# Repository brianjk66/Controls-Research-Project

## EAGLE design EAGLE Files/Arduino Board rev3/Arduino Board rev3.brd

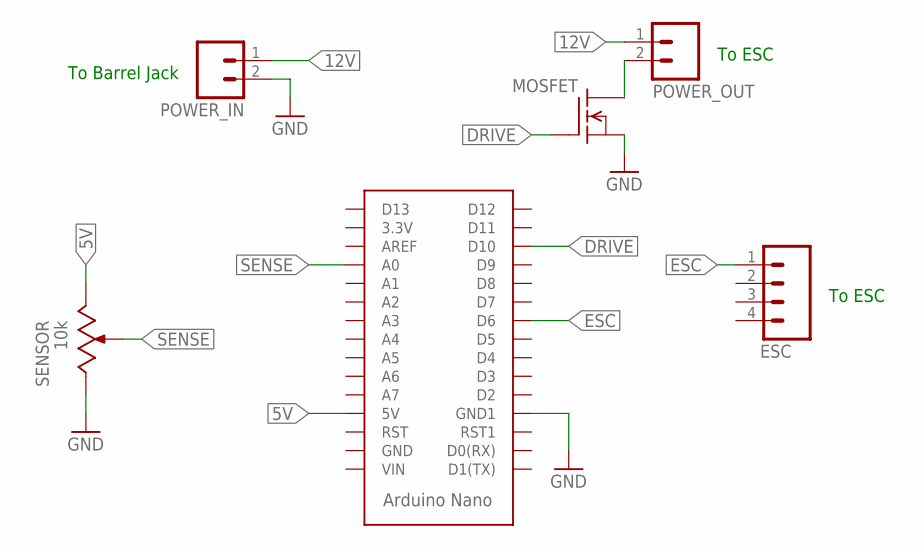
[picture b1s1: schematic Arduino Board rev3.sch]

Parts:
ARDUINO_NANO: ARDUINO_NANO
ESC: M04; 1X04
MOSFET: N-CHANNEL_MOSFETGENERIC; TO-220-SINK
POWER_IN: M02; 1X02
POWER_OUT: M02; 1X02
SENSOR: 10k; SV03A

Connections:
5V: ARDUINO_NANO.5V, SENSOR.3 (A)
12V: POWER_IN.1, POWER_OUT.1
DRIVE: ARDUINO_NANO.D10, MOSFET.1 (G)
ESC: ARDUINO_NANO.D6, ESC.1
GND: ARDUINO_NANO.GND1, MOSFET.3 (S), POWER_IN.2, SENSOR.1 (E)
unnamed: MOSFET.2 (D), POWER_OUT.2
SENSE: ARDUINO_NANO.A0, SENSOR.2 (S), SENSOR.2.1 (S)

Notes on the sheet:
To Barrel Jack
To ESC

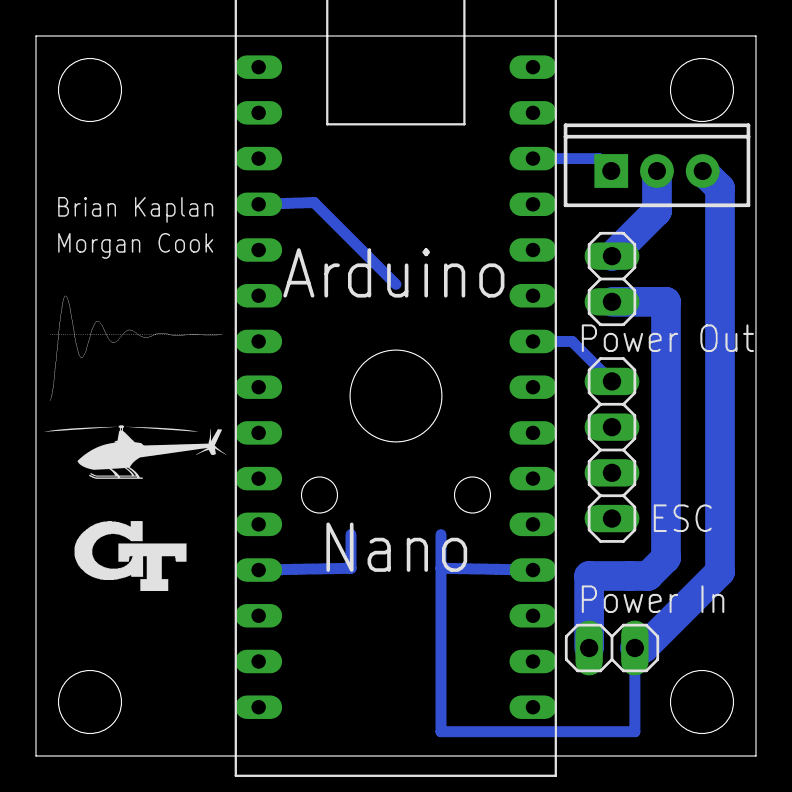
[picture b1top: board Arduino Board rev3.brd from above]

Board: 2 copper layers, 40.0 x 40.0 mm, 6 parts (1 on the bottom side), 7 nets.

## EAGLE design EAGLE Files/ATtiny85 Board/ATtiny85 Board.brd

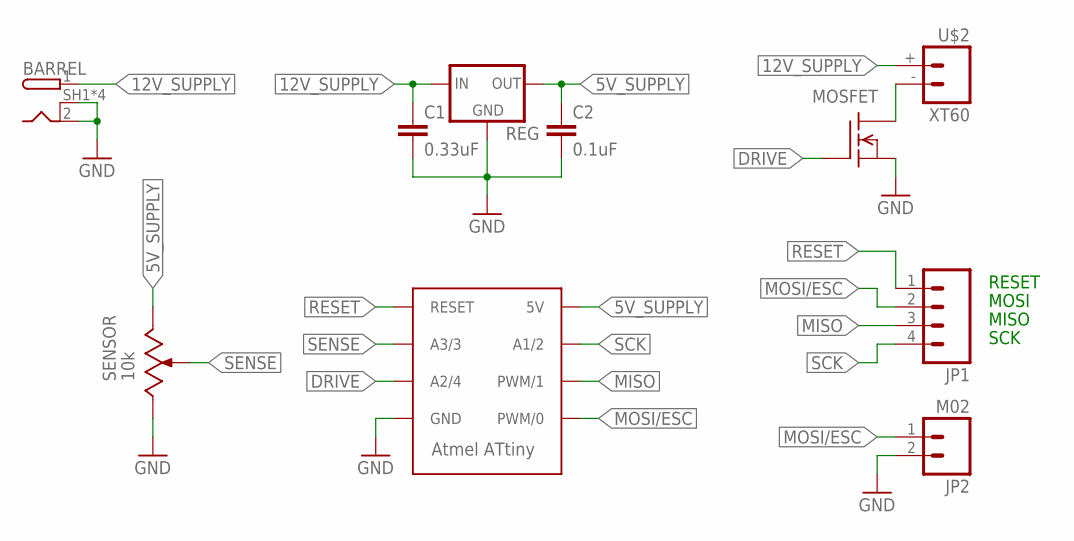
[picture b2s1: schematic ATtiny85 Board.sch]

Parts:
BARREL: PJ-082BH
C1: 0.33uF; 0805
C2: 0.1uF; 0805
JP1: M04; 1X04
JP2: M02; 1X02
MOSFET: SI2312; SOT-23
REG: L78L; SOT-89
SENSOR: 10k; SV03A
U$1: ATTINY; 8S2
U$2: XT60

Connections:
5V_SUPPLY: C2.1, REG.1 (OUT), SENSOR.1 (E), U$1.8 (5V)
12V_SUPPLY: BARREL.1 (PWR), C1.1, REG.3 (IN), U$2.+ (2)
DRIVE: MOSFET.1 (G), U$1.3 (A2/4)
GND: BARREL.2 (GND), BARREL.SH1 (SHIELD), BARREL.SH2 (SHIELD), BARREL.SH3 (SHIELD), BARREL.SH4 (SHIELD), C1.2, C2.2, JP2.2, MOSFET.2 (S), REG.2 (GND), REG.2.1 (GND), REG.2.2 (GND), SENSOR.3 (A), U$1.4 (GND)
MISO: JP1.3, U$1.6 (PWM/1)
MOSI/ESC: JP1.2, JP2.1, U$1.5 (PWM/0)
unnamed: MOSFET.3 (D), U$2.- (1)
RESET: JP1.1, U$1.1 (RESET)
SCK: JP1.4, U$1.7 (A1/2)
SENSE: SENSOR.2 (S), SENSOR.2.1 (S), U$1.2 (A3/3)

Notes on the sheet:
RESET
MOSI
MISO
SCK

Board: 2 copper layers, 10 parts (0 on the bottom side), 10 nets, no tracks yet.

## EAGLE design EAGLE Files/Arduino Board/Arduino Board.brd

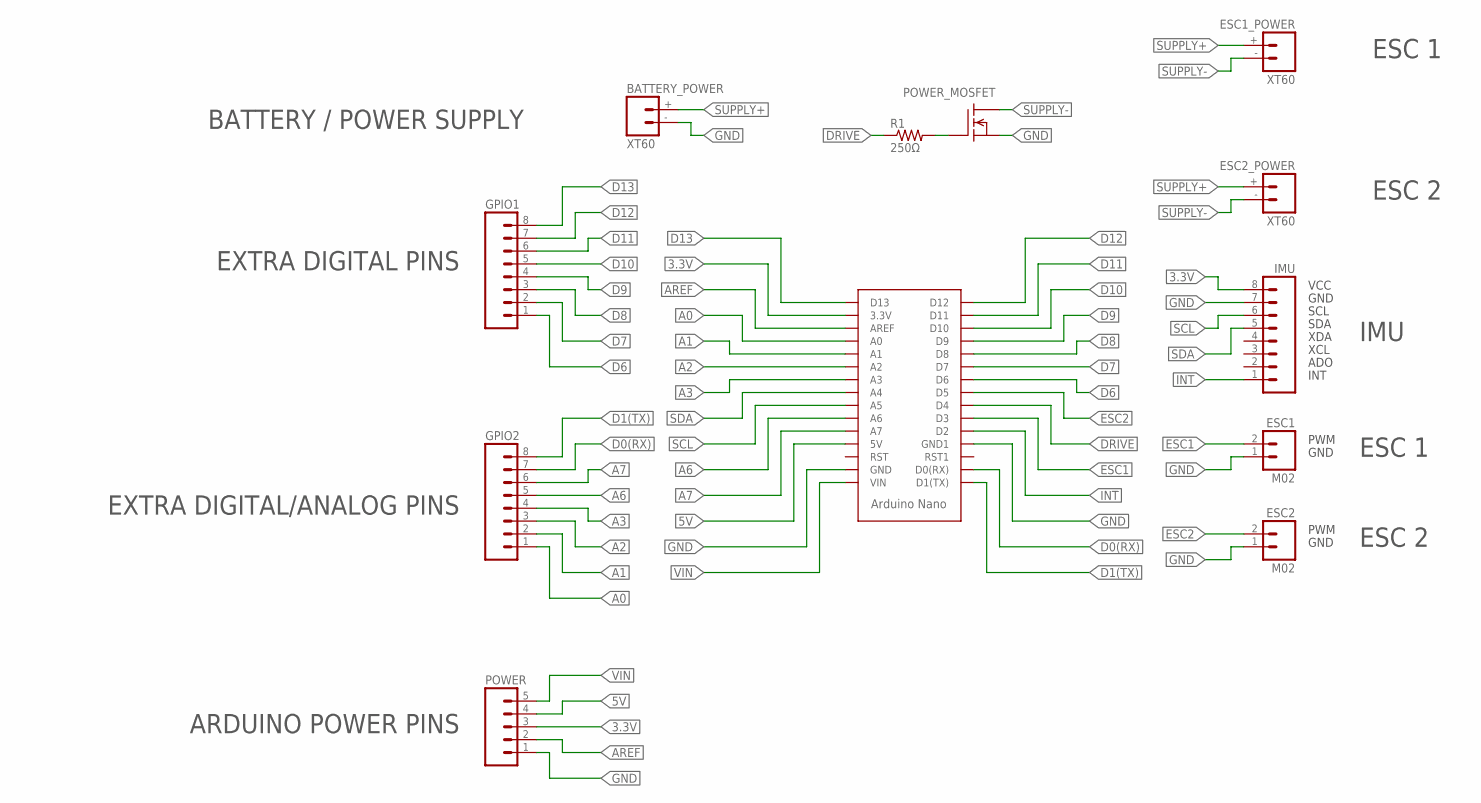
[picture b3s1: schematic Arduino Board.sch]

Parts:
BATTERY_POWER: XT60
ESC1, ESC2: M02; 1X02
ESC1_POWER, ESC2_POWER: XT60
GPIO1, GPIO2: M08; 1X08
IMU: M08; 1X08
POWER: M05; 1X05
POWER_MOSFET: N-CHANNEL_MOSFETGENERIC; TO-220-SINK
R1: 250Ω; AXIAL-0.4
U$1: ARDUINO_NANO

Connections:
3.3V: IMU.8, POWER.3, U$1.3.3V
5V: POWER.4, U$1.5V
A0: GPIO2.1, U$1.A0
A1: GPIO2.2, U$1.A1
A2: GPIO2.3, U$1.A2
A3: GPIO2.4, U$1.A3
A6: GPIO2.5, U$1.A6
A7: GPIO2.6, U$1.A7
AREF: POWER.2, U$1.AREF
D0(RX): GPIO2.7, U$1.D0(RX)
D1(TX): GPIO2.8, U$1.D1(TX)
D6: GPIO1.1, U$1.D6
D7: GPIO1.2, U$1.D7
D8: GPIO1.3, U$1.D8
D9: GPIO1.4, U$1.D9
D10: GPIO1.5, U$1.D10
D11: GPIO1.6, U$1.D11
D12: GPIO1.7, U$1.D12
D13: GPIO1.8, U$1.D13
DRIVE: R1.P$1 (1), U$1.D4
ESC1: ESC1.2, U$1.D3
ESC2: ESC2.2, U$1.D5
GND: BATTERY_POWER.- (1), ESC1.1, ESC2.1, IMU.7, POWER.1, POWER_MOSFET.3 (S), U$1.GND, U$1.GND1
INT: IMU.1, U$1.D2
unnamed: POWER_MOSFET.1 (G), R1.P$2 (2)
SCL: IMU.6, U$1.A5
SDA: IMU.5, U$1.A4
SUPPLY+: BATTERY_POWER.+ (2), ESC1_POWER.+ (2), ESC2_POWER.+ (2)
SUPPLY-: ESC1_POWER.- (1), ESC2_POWER.- (1), POWER_MOSFET.2 (D)
VIN: POWER.5, U$1.VIN

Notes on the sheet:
VCC
GND
SCL
SDA
XDA
XCL
ADO
INT
PWM
ESC 1
ESC 2
IMU
BATTERY / POWER SUPPLY
EXTRA DIGITAL PINS
EXTRA DIGITAL/ANALOG PINS
ARDUINO POWER PINS

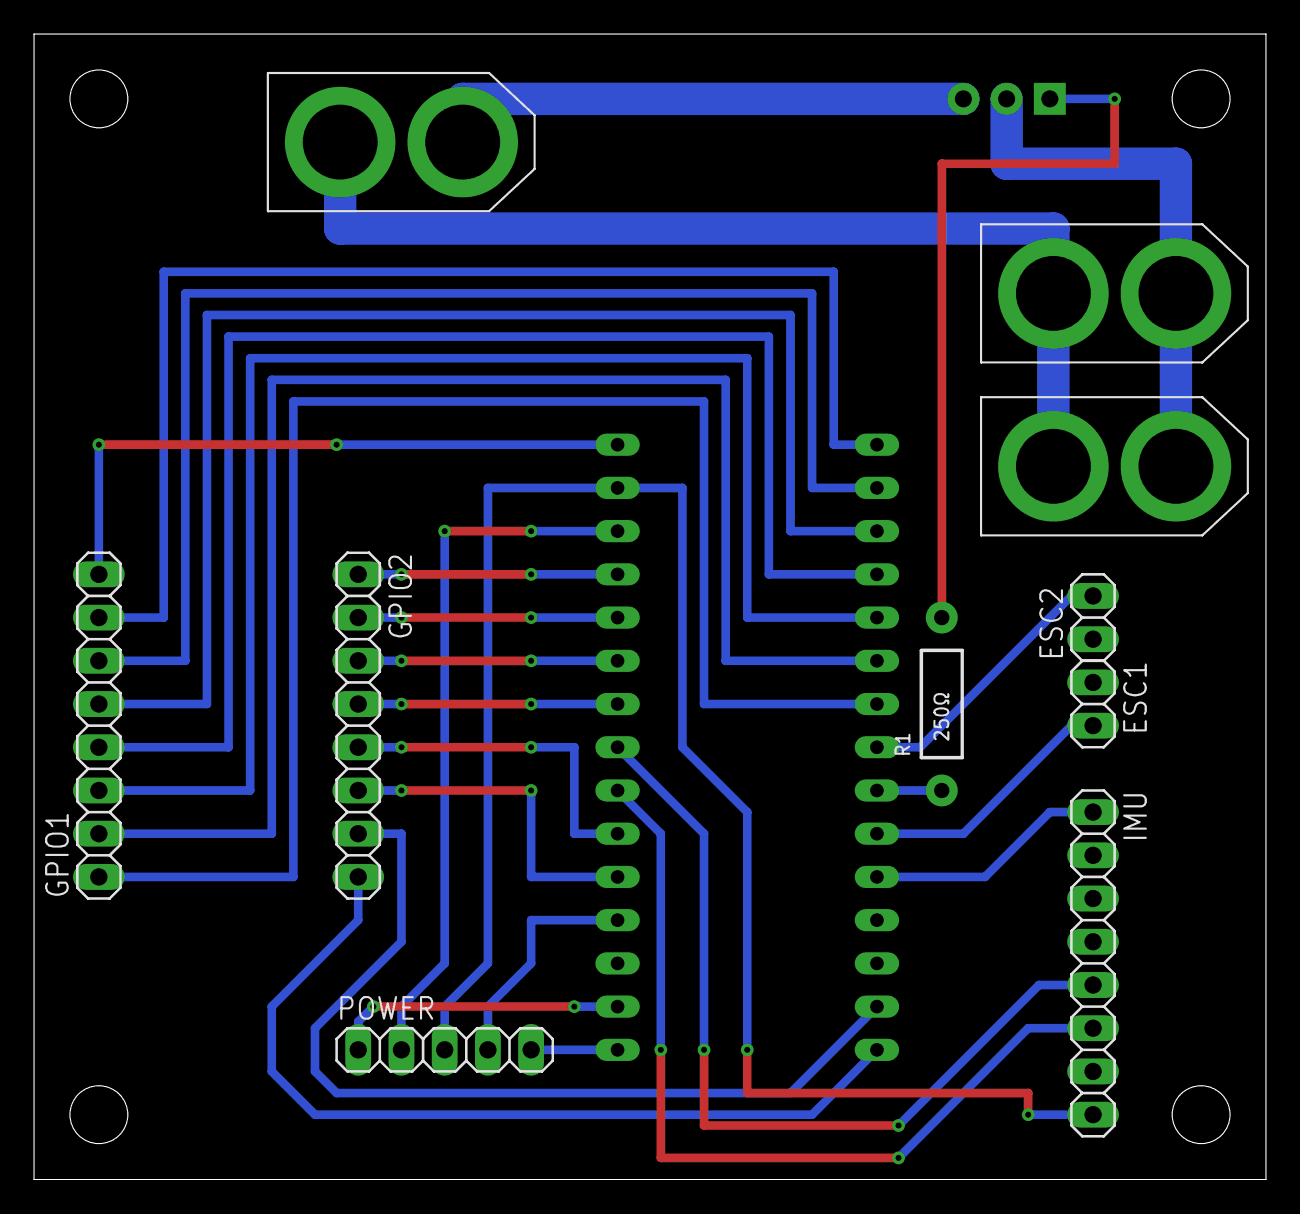
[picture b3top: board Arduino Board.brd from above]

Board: 2 copper layers, 72.4 x 67.3 mm, 12 parts (1 on the bottom side), 30 nets.

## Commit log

2017-11-17 Initial Commit of Current Project
    Arduino files, ordered parts, and other project files
2017-11-17 Test Commit
2017-11-17 CAD files initial upload
2017-11-17 Removed git commit test file
2017-11-17 Renamed CAD files
2017-11-17 Enlarged center hole for both MMs
2017-11-18 Reorganized CAD files
2017-11-18 Added 2MM gcode, .2mm layer thickness
2017-11-18 Fixed mounting hole problem
2017-11-18 Added gcode for DMM
2017-11-19 Added gcodes for 3D printing the arm and roll lock
2017-11-19 Added preliminary code for dual motor configuration
2017-11-19 Added dual motor pitch controller (gains are NOT tuned)
2017-11-21 Added rotating base 3D files
2017-11-21 Ok REALLY adding in the rotating base this time. Sorry.
2017-11-22 Added base to our files
2017-12-01 Created prelimiary PCB design to house project's microcontroller and electrical components
2017-12-01 Small modification to PID function to constrain value of iState more easily
2017-12-10 Added gitignore for EAGLE backup files (.b#2, .s#5, etc.)
2017-12-10 Tweaked gains, added constrain() function to PID integrator, and added cosine to thrust drive signal
2017-12-10 Small typo fix
2017-12-10 Corrected schematic error where MOSFET was wired incorrectly in circuit
2017-12-10 Added Arduino sketch for testing control of power MOSFET
2017-12-10 Fixed untracked files
2017-12-10 Added library file backups to .gitignore
2017-12-11 Updated default PID gains to more stable values
2017-12-11 Added voltage divider for simple battery monitoring
2017-12-16 Updated itemized receipts spreadsheet and added new order invoices
2017-12-18 Updated part orders spreadsheet and invoices
2017-12-29 Added new Hobby King and Banggood Orders to itemized receipts sheet
2018-01-07 Added barrel jack order from Digi-Key to itemized receipts spreadsheet
2018-01-07 Small fix to .gitignore file
2018-01-18 Added new Arrow order to itemized receipts spreadsheet
2018-01-18 Small changes to PCB design files from EAGLE software update
2018-01-18 Added new EAGLE design files for ATtiny85-based PCB
2018-01-18 Added new components to library for ATtiny85 PCB design
2018-01-18 Modified Rotating Base part to have fully parametrized dimensions and features
2018-01-21 Added new Arduino code for testing ESC control with the ATtiny85
2018-01-21 Updated BOM with headers and connectors
2018-01-25 Added several new sketches for testing the ATtiny85 with PWM, Serial, PID control, etc.
2018-01-25 Small fix to a few packages in library
2018-01-25 Enlarged and repositioned vias for easier milling and soldering
2018-01-25 Added standoffs to BOM and quotes from PCB fabrication and assembly plants
2018-01-25 New Base
2018-01-26 Cleaned up repository and modified .gitignore
2018-02-04 Updated .gitignore for Thumb.db Windows file
2018-02-04 Modified base with towers, made base with open slots for towers, made towers.
2018-02-04 Moved the Tower.stl file back to the 3D print files folder from SolidWorks Parts
2018-02-04 Fixed dimensions for printing on base and towers
2018-02-04 Reorganized .stl and .SLDPRT files into old Dual Motor, Misc (single motor included), and Teensy Configuration.
2018-02-04 Added single motor arm without a shaft. Potentially accidentally modified Arm.SLDPRT in Dual Motor and Single Motor Mount.SLDPRT in Misc.
2018-02-05 Actually added shaft.
2018-02-05 Made shaft size bigger, added a configuration for the arm file for 150mm with a centered ESC sheath, created a separate .STL file for it.
2018-02-05 Resized the square on shaft from 5.3mm to 4.9mm.
2018-02-05 Restructured software directory to distinguish between software for different microcontrollers (Arduino, ATtiny, and Teensy)
2018-02-05 Updated library to include the Teensy 3.2
2018-02-05 Created new PCB design for Teensy configuration
2018-02-05 Modified base and towers to accomodate new PCB design and better fit barrel jack and rocker switch
2018-02-07 Added a ton of .STL files for print testing in the studio, added new configurations to the base for testing.
2018-02-12 Updated itemized receipts spreadsheet with latest orders
2018-02-14 Hopefully saved the final design of towers, and 2 potential final bases.
2018-02-16 Added a longer dowel to the shaft, saved it under final shaft with square side length, bearing diameter, and dowel length in the .stl
2018-02-16 Added software for testing sensors and ESCs with Teensy 3.2
2018-02-16 Redid the equation to map sensor reading to angle. R^2 value is .99916 git status
2018-02-17 Added PID controller software for Teensy 3.2 with revised controller code
2018-02-17 Added verified default gains, changed macro from PERIOD to FREQUENCY, converted filter from 10 to 100 point averager, and added rounding for measurement precision
2018-02-18 Increased ESC Test code baud rate to 115200 for faster response time
2018-02-21 Updated .gitignore
2018-02-21 Reorganized EAGLE design files and added second revision Arduino board design
2018-02-21 Renamed 'Itemized Receipts.xlsx' to 'Expense Report.xlsx' and added latest purchases to the spreadsheet
2018-02-22 Updated expense report with latest Amazon order and revised HobbyKing order with refunded motors
2018-02-22 Created third revision of Arduino board design to feature a through-hole MOSFET, also made some small changes to EAGLE library
2018-02-22 Updated bill of materials to reflect latest part selections and orders
2018-02-22 Removed old/outdated bill of materials from earlier build
2018-02-22 Renamed 'Teensy Build BOM.xlsx' to 'Bill of Material.xlsx'
2018-02-22 Moved all old Arduino code from older builds into an archive folder
2018-02-22 Added new Arduino software files for testing and running the latest build
2018-02-23 Changed Arduino code to reflect new PCB (revision 3) configuration
2018-02-24 Added improved filtering to analog readings, converted from doubles to floats for improved computation time, and changed starting sequence to arm ESC by default
2018-02-25 Added latest orders and invoices to Bill of Materials and Expense Report
2018-02-25 Finalized PCB designs and generated Gerber files for manufacturing
2018-02-25 Added presentation for introducing project to students and template for writing user guide
2018-02-27 Added invoice from latest Arrow order to expense report
2018-02-27 Added finalized presentation slides
2018-02-27 Increased baud rate and added arming by default to ESC testing code
2018-02-28 Added dowel to tower, made tentative final STL files folder.
2018-03-01 Changed base to accomodate the dowels.
2018-03-02 Added most recent Amazon order invoice to expense report
2018-03-02 Added macro for sensor pin number
2018-03-02 Changed baud rate back to 115200 for consistency among all Arduino sketches
2018-03-02 Added new power adapter to bill of materials to replace old faulty supply
2018-03-11 Added proper delays for arming and calibrating plus serial printouts to show user when they complete
2018-03-11 Added resetSystem() function for use during startup, pauses, tuning, etc. to prevent against filter and derivative spiking. Added updatePID flag to limit frequency of serial printouts to once per ref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
2018-03-12 Extended overshoot dowels to 10mm and added holes through dowels to support M4 bolts for added structural stability
2018-03-12 Added latest orders to Expense Report and updated Bill of Materials with M4 screws and nuts for new Tower modification
2018-04-01 Added most recent Amazon Order for heatshrink tubing to expense report
2018-04-01 Added heat shrink tubing to Bill of Materials
2018-04-01 Added Home Depot order for wire strippers to expense report
2018-04-07 Minor change to sensor test code
2018-04-07 Modified PID controller code to print properly formatted data for serial plotting
2018-04-07 Added new schematic for full eletrical system layout
2018-04-07 Added serial plotting settings and test software
2018-04-07 Small fix to parentheses in sensor test code
2018-04-07 Final touches for official software release
2018-04-25 Added test for simultaneously measuring angle and controlling ESC
2018-05-10 Finalized expense report for submission to Georgia Tech
